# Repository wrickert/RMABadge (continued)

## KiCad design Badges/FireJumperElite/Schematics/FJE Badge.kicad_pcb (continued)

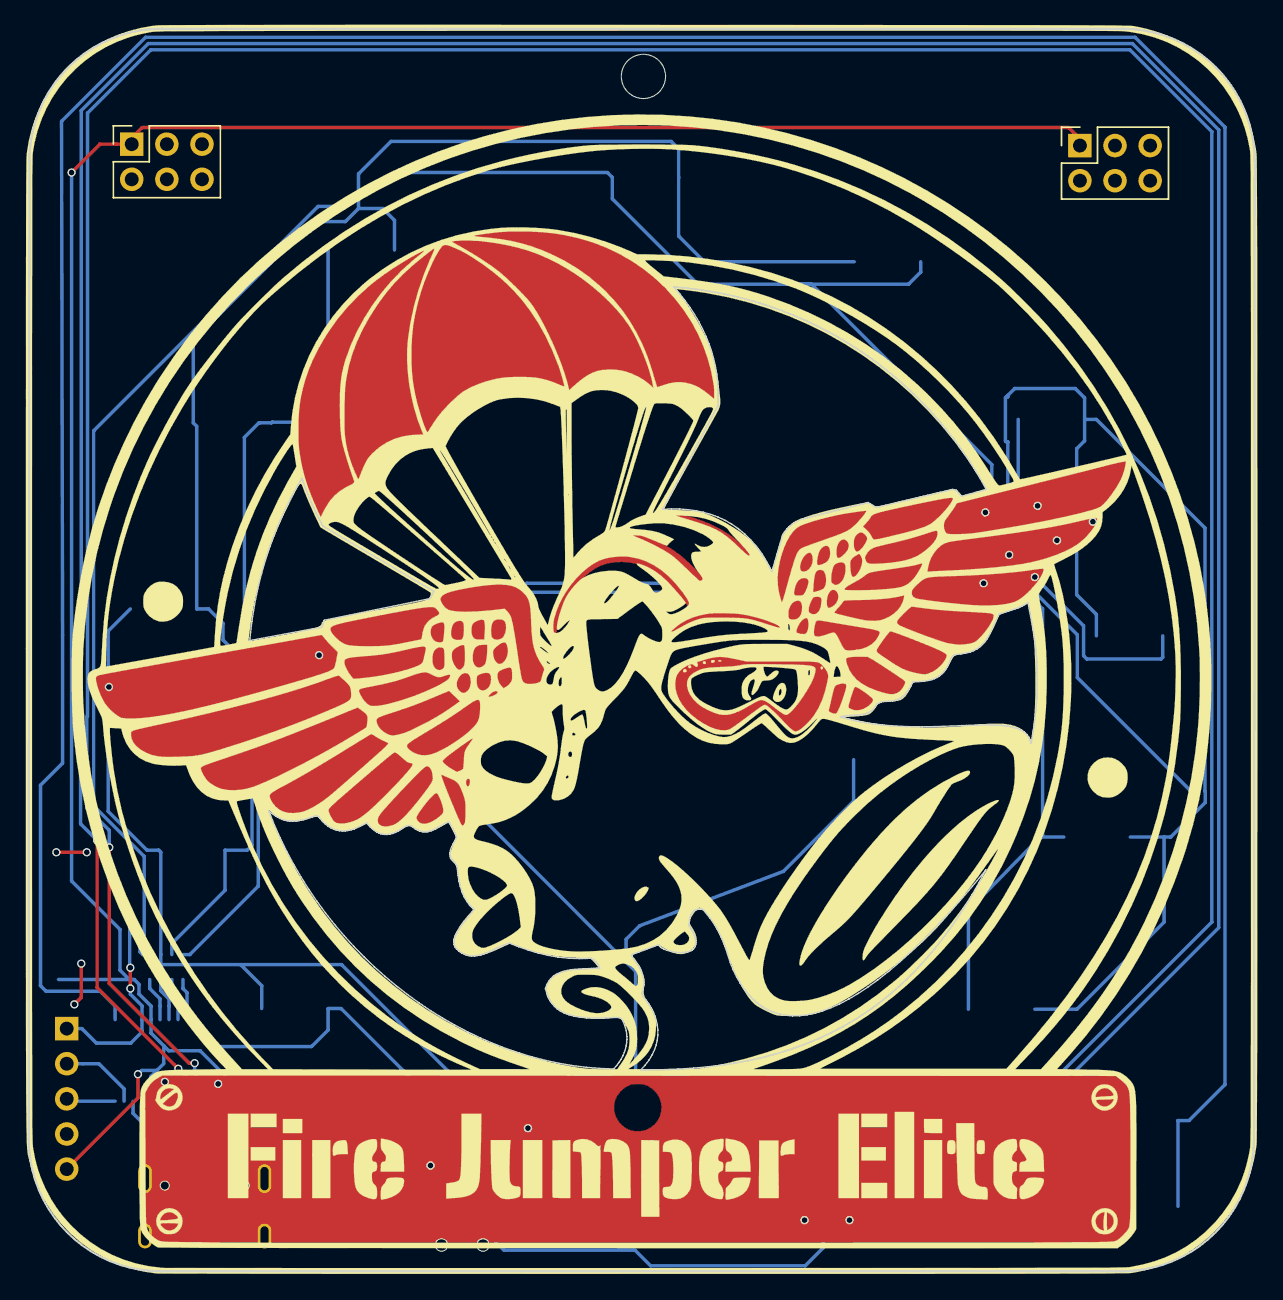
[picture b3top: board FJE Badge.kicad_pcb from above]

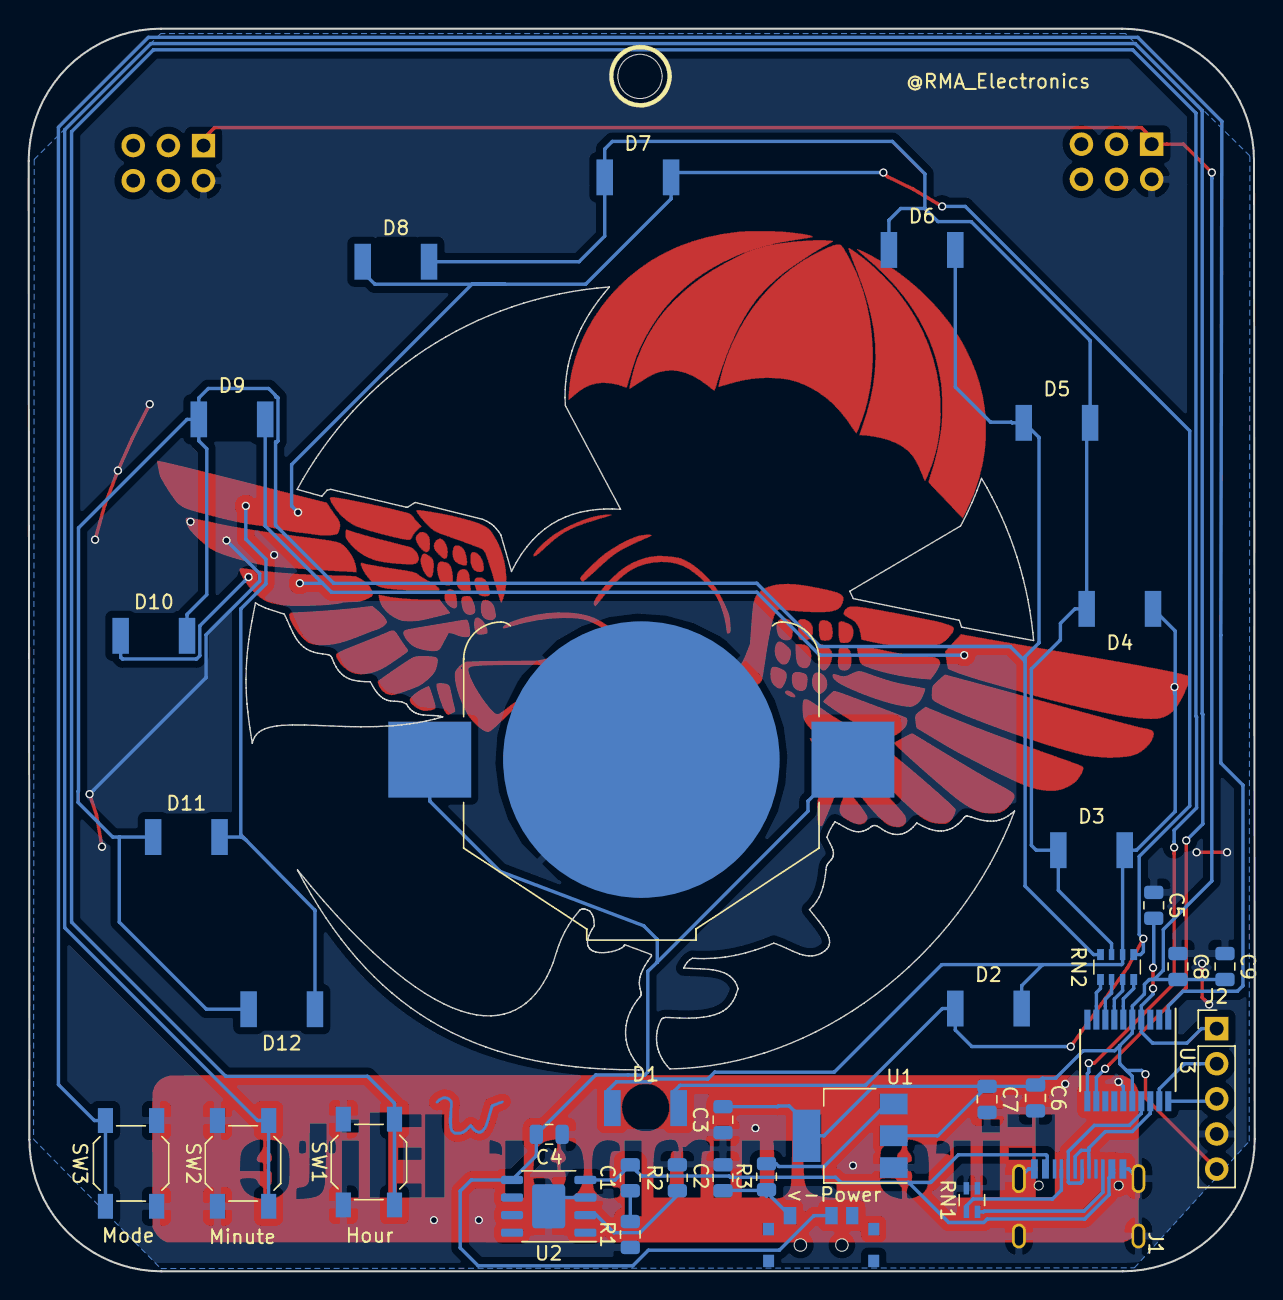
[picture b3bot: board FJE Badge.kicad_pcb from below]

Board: 2 copper layers, 88.7 x 89.8 mm, 39 parts (37 on the bottom side), 26 nets.

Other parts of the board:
<-Power: SW3; SK-3296S_switch
Ref**: Val**; W

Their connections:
unnamed 12: <-Power.3; also elsewhere on the board
VDDA: <-Power.2; also elsewhere on the board

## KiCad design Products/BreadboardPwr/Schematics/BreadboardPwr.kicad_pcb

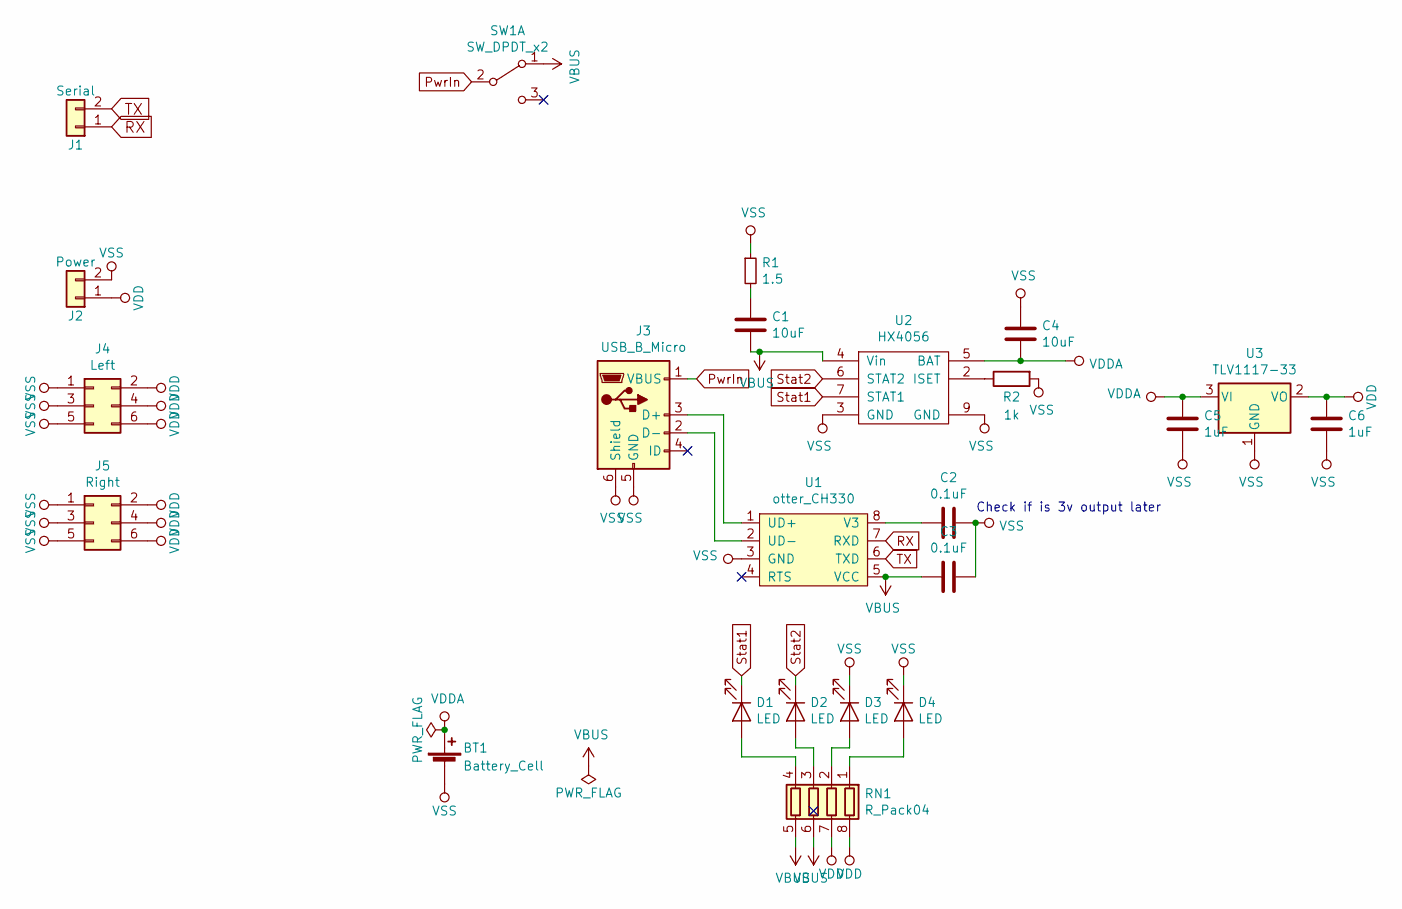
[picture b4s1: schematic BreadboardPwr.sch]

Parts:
BT1: Battery_Cell; BatteryHolder_Keystone_3008_1x2450
C1, C4: 10uF; C_0805_2012Metric
C2, C3: 0.1uF; C_0805_2012Metric
C5, C6: 1uF; C_0805_2012Metric
D1, D2, D3, D4: LED; LED_0603_1608Metric
J1: Serial; PinHeader_1x02_P2.54mm_Vertical
J2: Power; PinHeader_1x02_P2.54mm_Vertical
J3: USB_B_Micro; USB_Micro-B_Jing
J4: Left; PinHeader_2x03_P2.54mm_Vertical
J5: Right; PinHeader_2x03_P2.54mm_Vertical
R1: 1.5; R_0805_2012Metric
R2: 1k; R_0805_2012Metric
RN1: R_Pack04; R_Array_Convex_4x0603
SW1: SW_DPDT_x2; SK-3296S_switch
U1: otter_CH330; SOIC-8_3.9x4.9mm_P1.27mm
U2: HX4056; SOIC-8-1EP_3.9x4.9mm_P1.27mm_EP2.29x3mm
U3: TLV1117-33; SOT-223-3_TabPin2

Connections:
unnamed: C1.1, R1.2
unnamed: C2.1, U1.8 (V3)
unnamed: D1.2 (A), RN1.4 (R4.1)
unnamed: D2.2 (A), RN1.3 (R3.1)
unnamed: D3.2 (A), RN1.2 (R2.1)
unnamed: D4.2 (A), RN1.1 (R1.1)
unnamed: J3.2 (D-), U1.2 (UD-)
unnamed: J3.3 (D+), U1.1 (UD+)
unnamed: R2.1, U2.2 (ISET)
PwrIn: J3.1 (VBUS), SW1.2 (B)
RX: J1.1, U1.7 (RXD)
Stat1: D1.1 (K), U2.7 (STAT1)
Stat2: D2.1 (K), U2.6 (STAT2)
TX: J1.2, U1.6 (TXD)
VBUS: C1.2, C3.2, RN1.5 (R4.2), RN1.6 (R3.2), SW1.1 (A), U1.5 (VCC), U2.4 (Vin)
VDD: C6.1, J2.1, J4.2, J4.4, J4.6, J5.2, J5.4, J5.6, RN1.7 (R2.2), RN1.8 (R1.2), U3.2 (VO)
VDDA: BT1.1 (+), C4.2, C5.1, U2.5 (BAT), U3.3 (VI)
VSS: BT1.2 (-), C2.2, C3.1, C4.1, C5.2, C6.2, D3.1 (K), D4.1 (K), J2.2, J3.5 (GND), J3.6 (Shield), J4.1, J4.3, J4.5, J5.1, J5.3, J5.5, R1.1, R2.2, U1.3 (GND), U2.3 (GND), U2.9 (GND), U3.1 (GND)

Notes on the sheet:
Check if is 3v output later

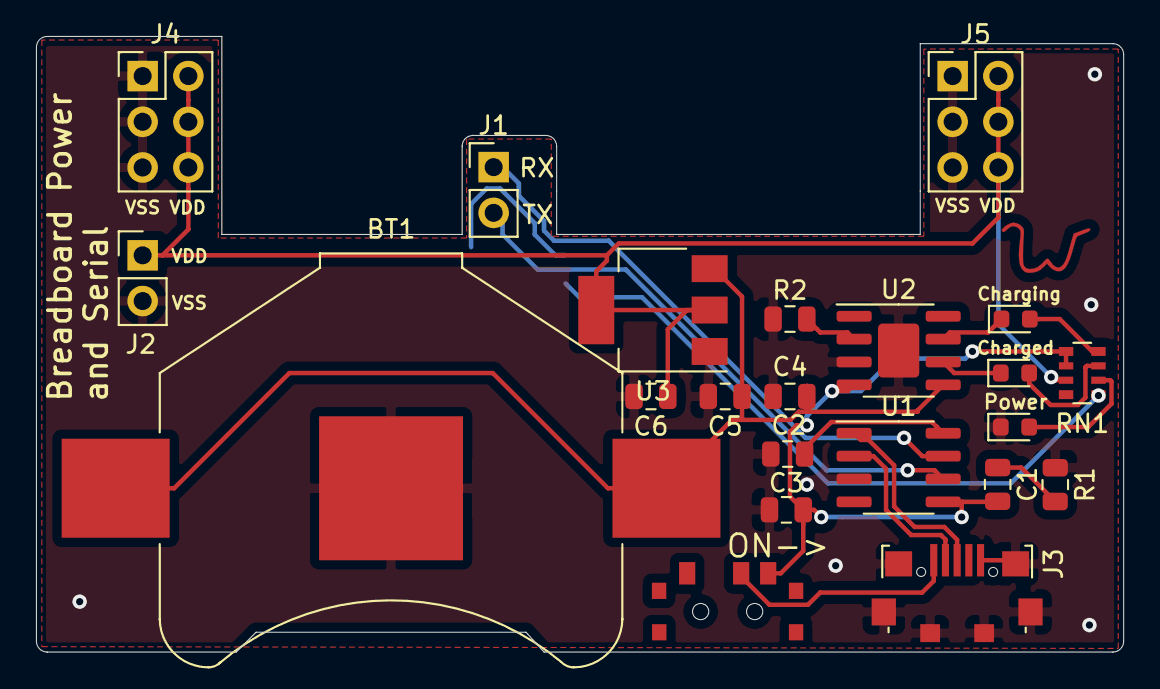
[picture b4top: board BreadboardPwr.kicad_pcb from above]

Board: 2 copper layers, 60.4 x 34.2 mm, 24 parts (1 on the bottom side), 18 nets.

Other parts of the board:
Ref**: Val**; W

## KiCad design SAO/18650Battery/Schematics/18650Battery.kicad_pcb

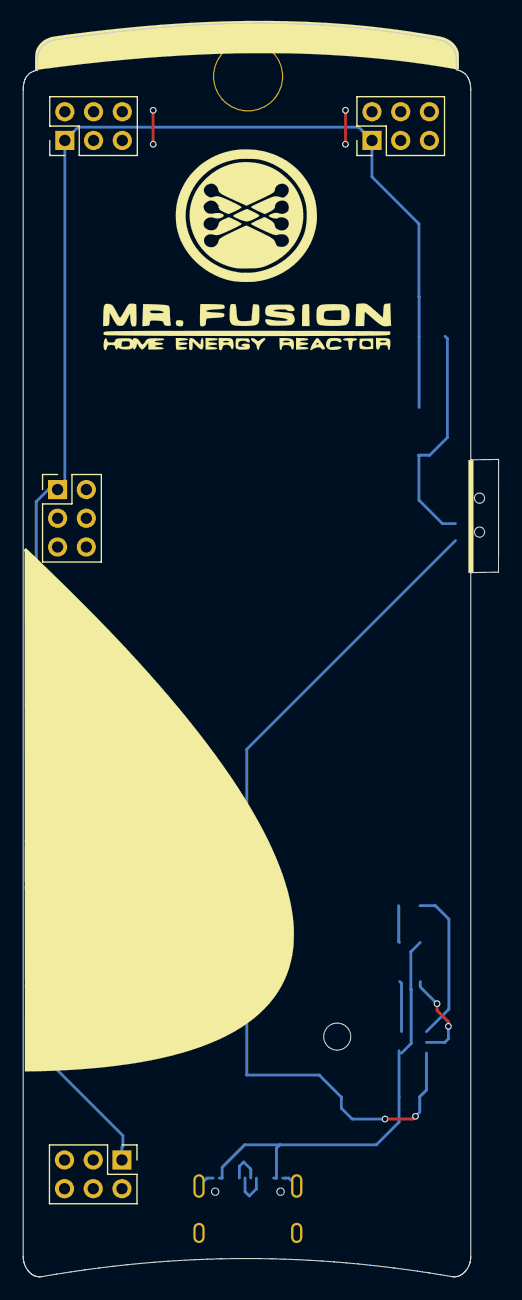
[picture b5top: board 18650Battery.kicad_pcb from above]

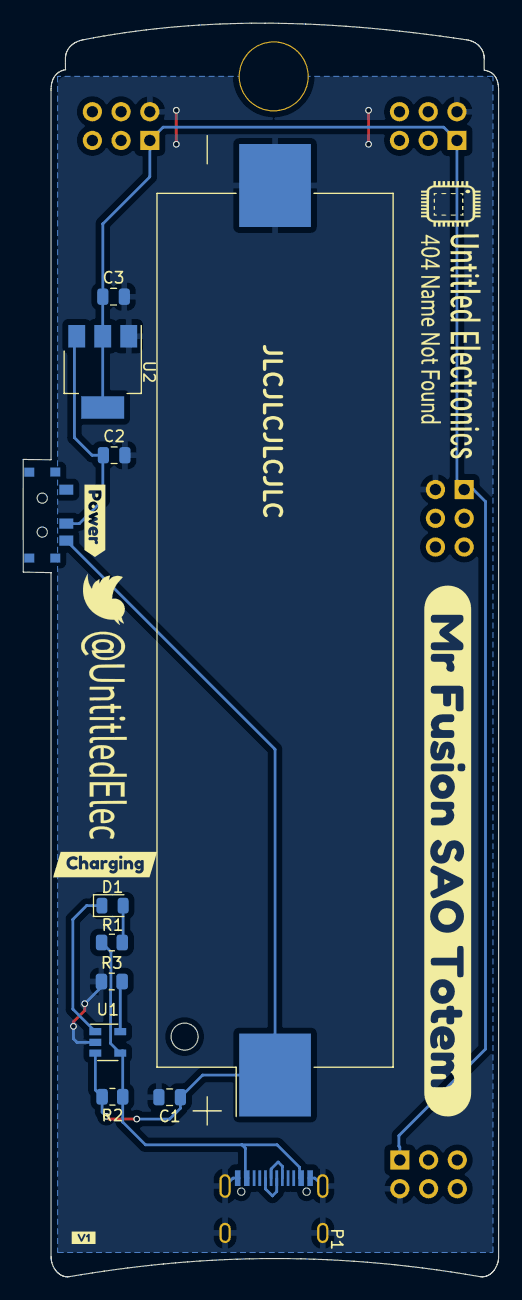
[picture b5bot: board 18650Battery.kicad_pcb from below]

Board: 2 copper layers, 42.0 x 110.9 mm, 22 parts (18 on the bottom side), 8 nets.

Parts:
BT1: Battery_Cell; BatteryHolder_18650
C1: 10uF; C_0805_2012Metric
C2, C3: 1uF; C_0805_2012Metric
D1: LED_Small; LED_0805_2012Metric
J1, J2, J3, J4: Conn_02x03_Odd_Even; PinHeader_2x03_P2.54mm_Vertical
P1: USB_C_Plug_corrected; USB_C_Receptical-Jing
Power->1: SW3; SK-3296S_switch
R1: 1k; R_0805_2012Metric
R2: Charger Bypass; R_0805_2012Metric
R3: R_Small; R_0805_2012Metric
Ref**: Val**; Twitter
Ref**#2: Val**; UELogoSmall
U1: HX4055M; SOT-23-5
U2: TLV1117-33; SOT-223-3_TabPin2
svg2mod, svg2mod#2, svg2mod#3, svg2mod#4: G***; svg2mod

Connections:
unnamed: C2.1, Power->1.2 (B), U2.3 (VI)
unnamed: D1.1 (K), U1.1 (Chrg)
unnamed: D1.2 (A), R1.1
unnamed: R3.2, U1.5 (PROG)
VBUS: P1.A4 (VBUS), P1.A9 (VBUS), P1.B4 (VBUS), P1.B9 (VBUS), R1.2, R2.1, U1.4 (VCC)
VCC: C3.1, J1.1, J2.1, J3.1, J4.1, U2.2 (VO)
VDDA: BT1.1 (+), C1.1, Power->1.1 (A), R2.2, U1.3 (Bat)
VSS: BT1.2 (-), C1.2, C2.2, C3.2, J1.2, J2.2, J3.2, J4.2, P1.A1 (GND), P1.A12 (GND), P1.B1 (GND), P1.B12 (GND), P1.S1 (SHIELD), R3.1, U1.2 (Gnd), U2.1 (GND)

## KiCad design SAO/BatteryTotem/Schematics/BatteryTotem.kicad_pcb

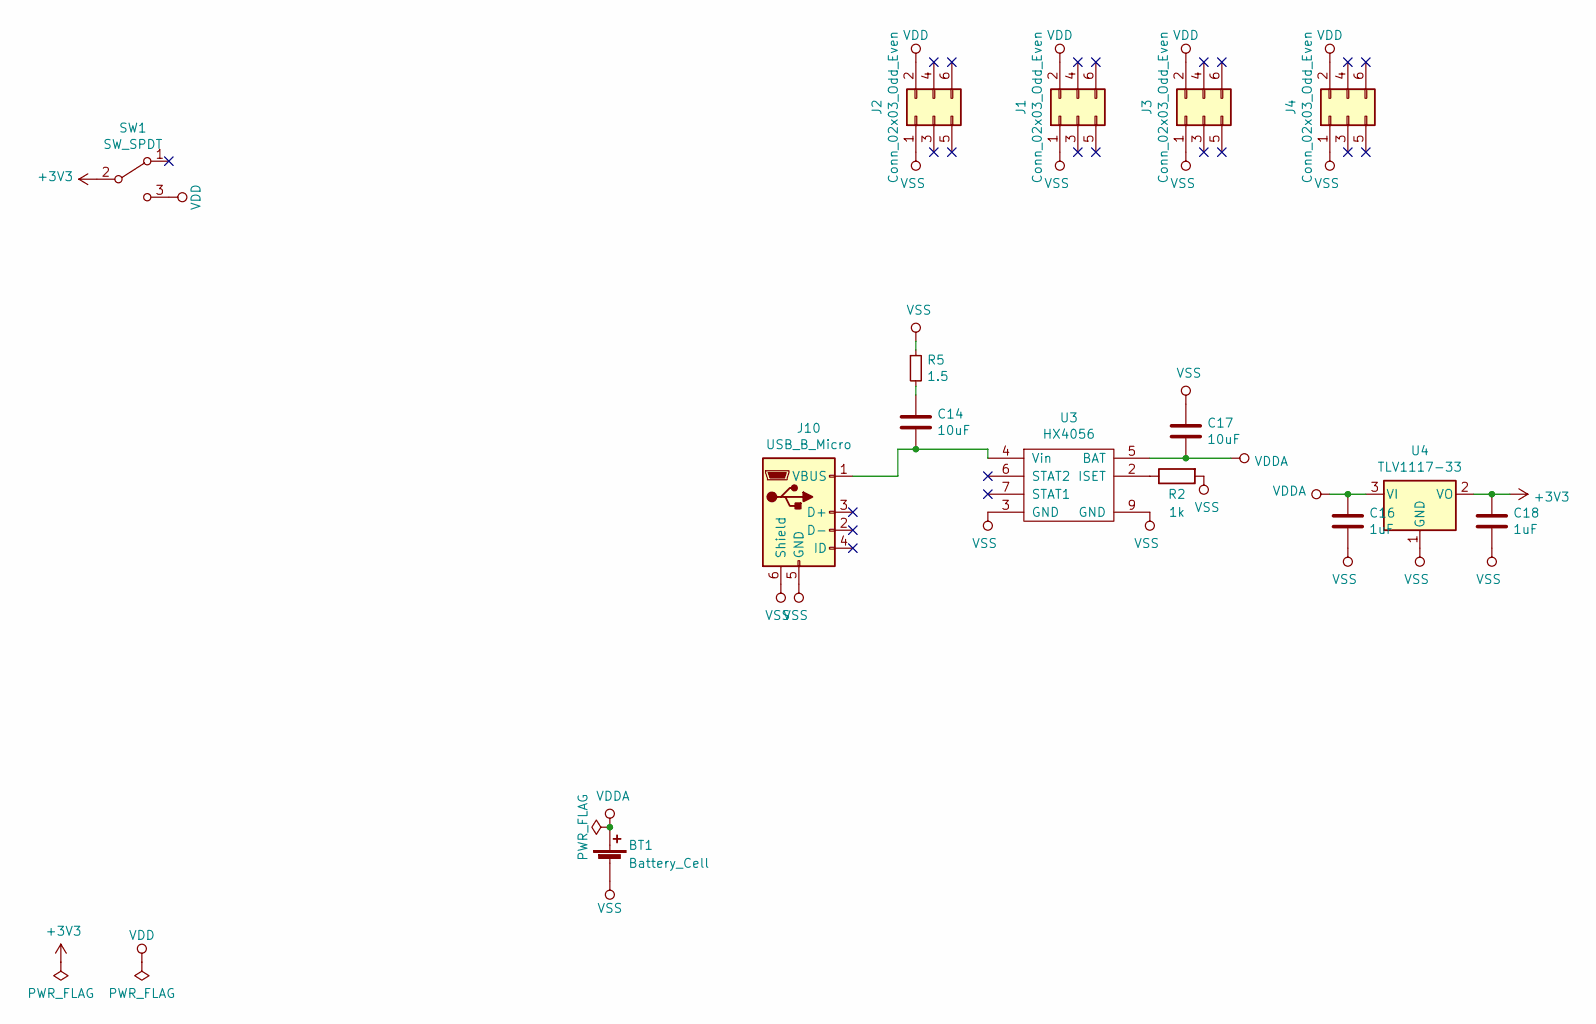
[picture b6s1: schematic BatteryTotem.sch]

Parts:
BT1: Battery_Cell; BatteryHolder_Keystone_3008_1x2450
C14, C17: 10uF; C_0805_2012Metric
C16, C18: 1uF; C_0805_2012Metric
J1, J2, J3, J4: Conn_02x03_Odd_Even; PinHeader_2x03_P2.54mm_Vertical
J10: USB_B_Micro; USB_Micro-B_Jing
R2: 1k; R_0805_2012Metric
R5: 1.5; R_0805_2012Metric
SW1: SW_SPDT; SK-3296S_switch
U3: HX4056; HSOP-8-1EP_3.9x4.9mm_P1.27mm_EP2.41x3.1mm_ThermalVias
U4: TLV1117-33; SOT-223-3_TabPin2

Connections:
+3V3: C18.1, SW1.2 (B), U4.2 (VO)
unnamed: C14.1, R5.2
unnamed: C14.2, J10.1 (VBUS), U3.4 (Vin)
unnamed: R2.1, U3.2 (ISET)
VDD: J1.2, J2.2, J3.2, J4.2, SW1.3 (C)
VDDA: BT1.1 (+), C16.1, C17.2, U3.5 (BAT), U4.3 (VI)
VSS: BT1.2 (-), C16.2, C17.1, C18.2, J1.1, J2.1, J3.1, J4.1, J10.5 (GND), J10.6 (Shield), R2.2, R5.1, U3.3 (GND), U3.9 (GND), U4.1 (GND)

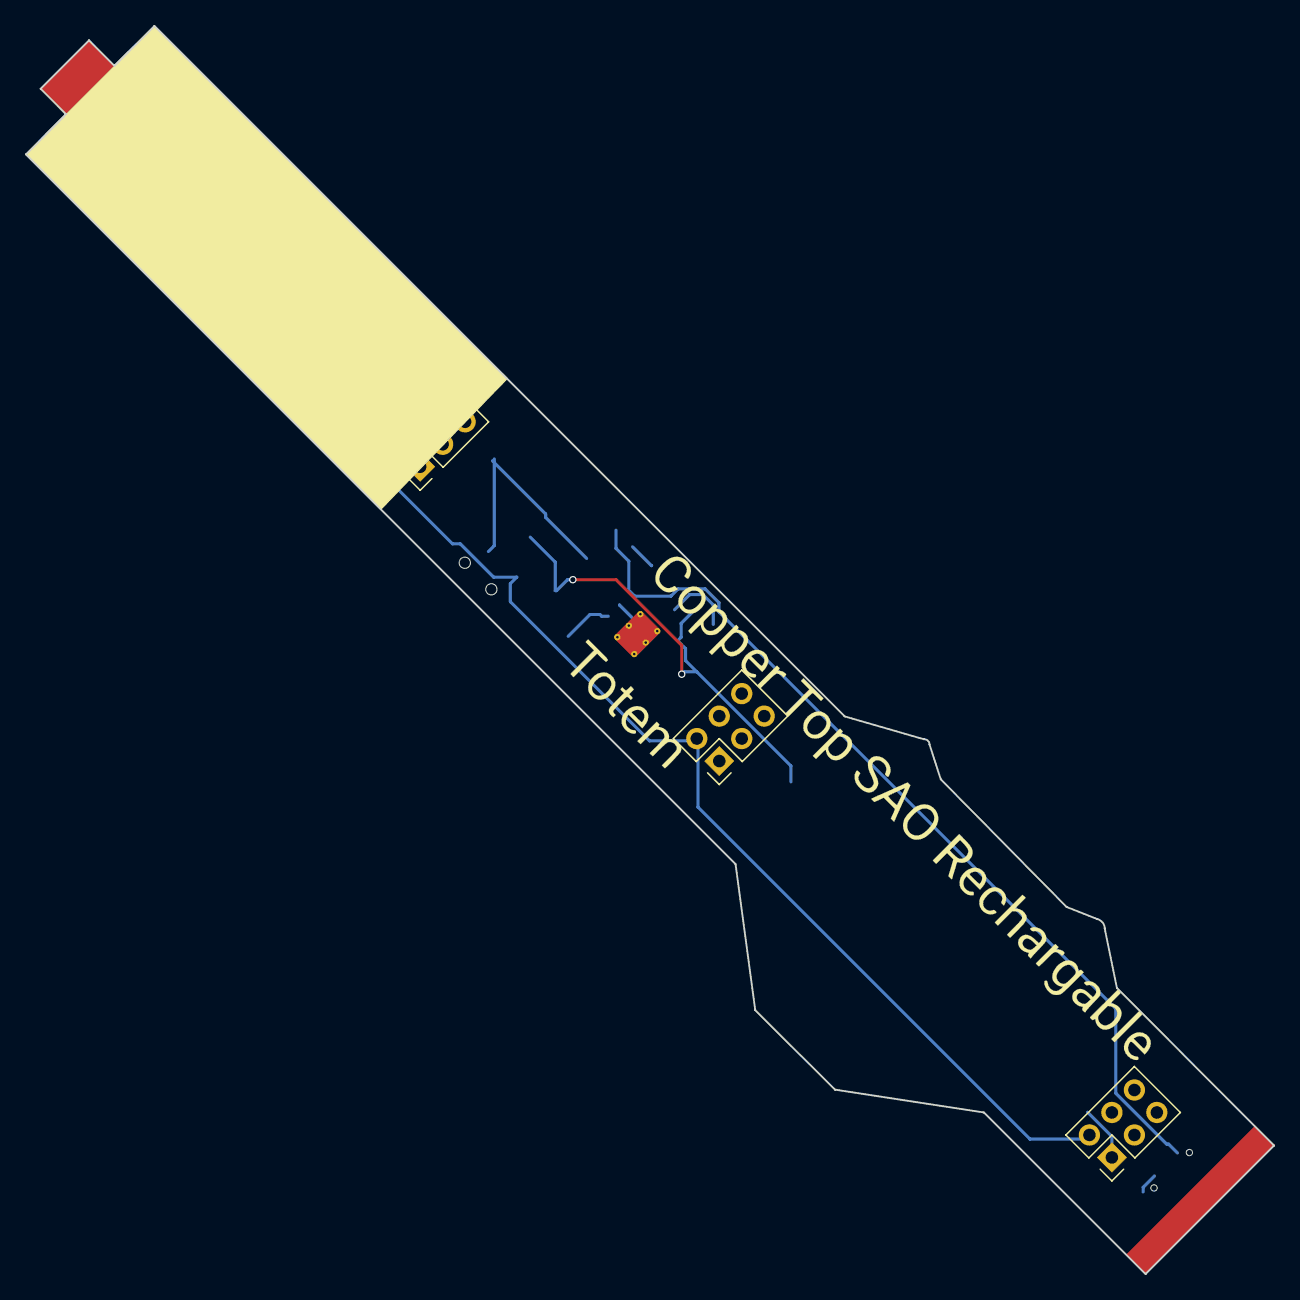
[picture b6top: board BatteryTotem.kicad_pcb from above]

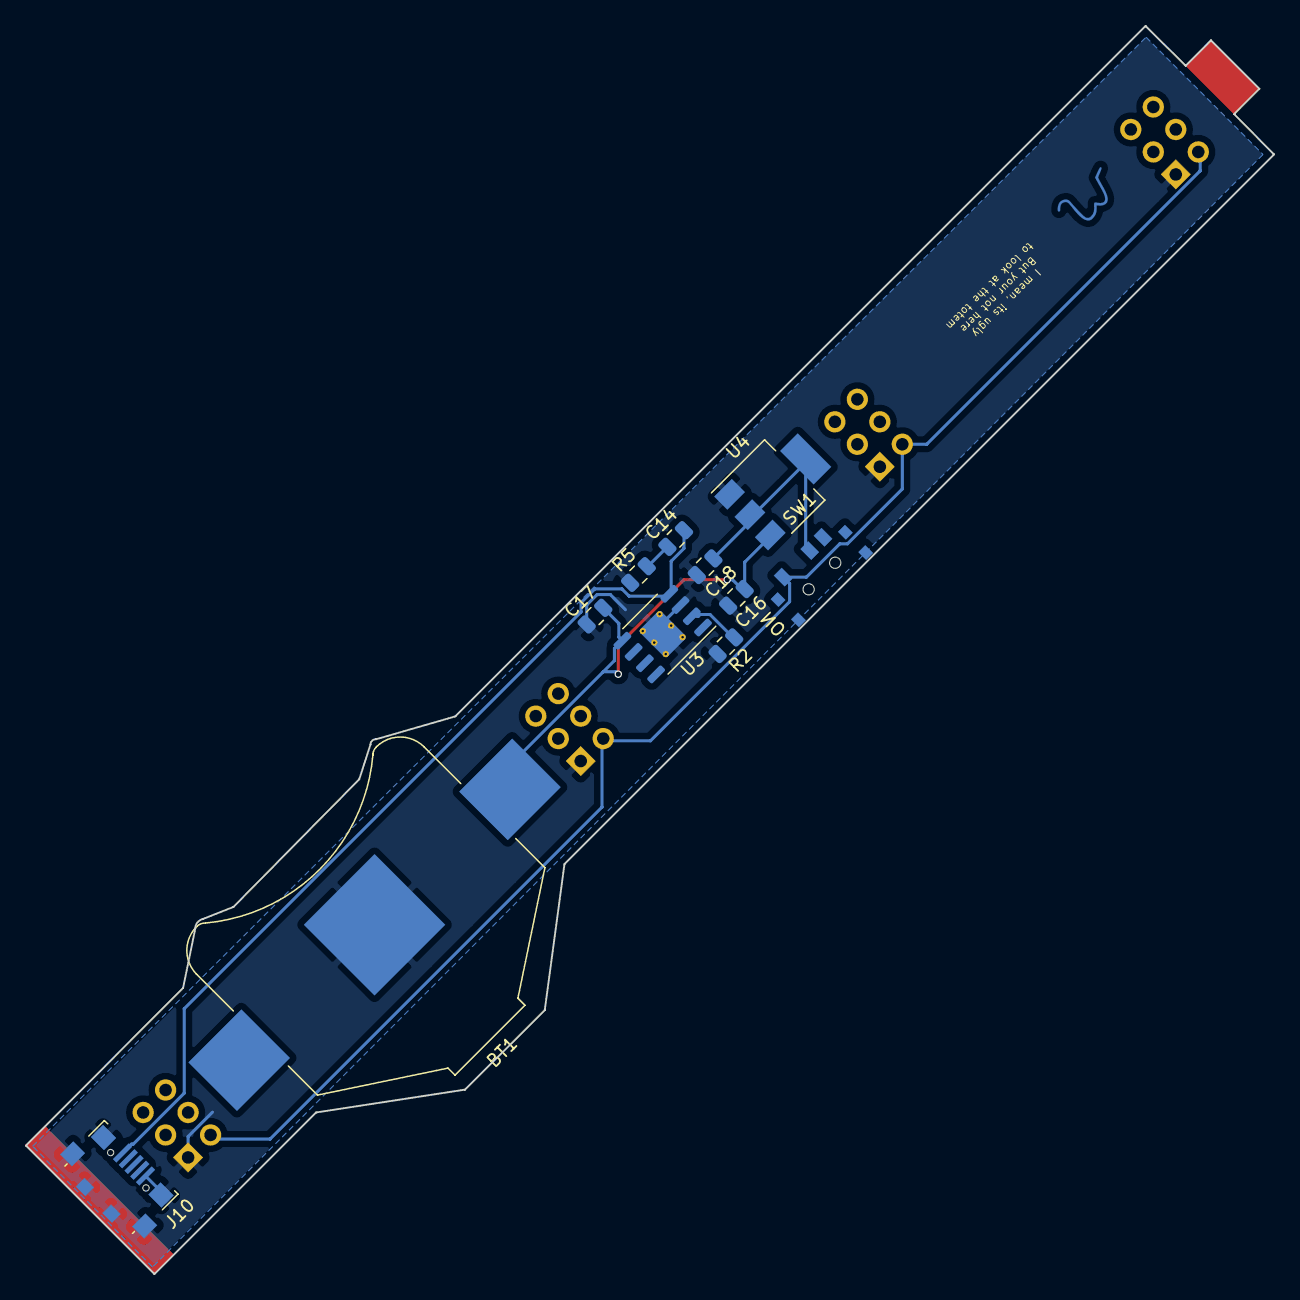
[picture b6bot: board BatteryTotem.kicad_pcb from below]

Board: 2 copper layers, 99.7 x 99.7 mm, 16 parts (12 on the bottom side), 7 nets.

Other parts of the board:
Ref**: Val**; W
